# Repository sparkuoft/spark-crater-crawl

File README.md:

# spark-crater-crawl

Crater Crawl runs on **two Arduino Mega 2560s** joined by a serial cable. How it all
fits together, the wiring, and a step-by-step test plan are in
[docs/INTEGRATION.md](docs/INTEGRATION.md).

| Folder | What it is | Board |
| --- | --- | --- |
| `crater_crawl/` | Game sketch: game FSM, pillars and sequencer, LED strip, Serial console, unit tests | Game Mega |
| `crater_crawl_wheels/` | Wheels sketch (Alice): steering wheels, character steppers, plus Tracking's sensors | Wheels Mega |
| `hardware_tests/` | Small check sketches: LED strip, link cable, Tracking's inputs | either |
| `laptop/` | Runs the game sketch's logic on a computer, for testing without hardware | laptop |
| `Photo Interrupt Sensor/` | Tracking's PCB, tests and docs | |
| `demo/` | Demo script for the laptop build | |

## Arduino IDE setup

Board: **Arduino Mega or Mega 2560**. Install these from the Library Manager:
FastLED, TimerOne, TCA9548A, Servo.

Open `crater_crawl/crater_crawl.ino` and upload it to the Game Mega; open
`crater_crawl_wheels/crater_crawl_wheels.ino` and upload it to the Wheels Mega.
Serial Monitor: 115200 baud, "Newline". On the Game Mega, type `?` for status and
`t` to run the unit tests.

## Laptop build

    clang++ -std=c++11 -Wall -Wextra -pthread -Icrater_crawl/src -o test laptop/main.cpp crater_crawl/src/*.cpp
    ./test --test                              # unit tests
    ./test < demo/fall_design_review.txt       # demo round
    ./test --live                              # play in real time

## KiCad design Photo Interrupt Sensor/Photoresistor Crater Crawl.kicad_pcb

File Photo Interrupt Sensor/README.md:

# Character tracking (C)

> **Where the files are (2026-11-22):** `CharacterModule.h/.c` now live in
> `crater_crawl_wheels/src/tracking/`, because they're built into the Wheels Mega
> firmware. `CharacterController.*`, the tests and the PCB stay in this folder, and
> `tests/run_tests.py` finds the module in its new place. The hardware callbacks
> are in `crater_crawl_wheels/tracking_hal.cpp`. See `docs/INTEGRATION.md`.

`CharacterModule.c` and `CharacterController.c` implement the tracking logic in
C11 with fixed storage and no dynamic allocation. They do not include Arduino
or `shared_state.h`. C++ callers can include the headers directly because the
function declarations have `extern "C"` guards. Compile the `.c` files as C.

The physical pin mapping, encoder/mux driver, interrupt attachment and Wheels
transport are supplied through callbacks. No hardware driver or connection to
the existing game FSM/main loop is implemented here (those are the next step).

## Responsibilities

- One `CharacterModule` per player: encoder offset/angle validity, nonblocking
  homing, reference refresh and a queue of pillar-switch contact events.
- One `CharacterController` for the two players: updates both modules, validates
  the angle pair, detects circular proximity, and optionally requests a paired
  movement response. It never changes lives, lockouts or the game phase.
- The future game adapter publishes valid angles and drains both players'
  pillar queues before calling `game_fsm_update()`. Player-pair notifications
  are separate from pillar hits and must not be sent to `game_on_collision()`.

## Public API and initialization

Start with zero-initialized module/controller storage. Obtain a config with
`character_default_config()`, set player ID, actual encoder channel and hardware
callbacks, and check `character_init()`'s bool result. Initialization validates
configuration but does not access hardware or start motors. A failed init does
not modify the destination. Do not reinitialize active modules/controllers.

Provide all `CharacterHardware` callbacks except `identify_pillar`, which is
optional. A context pointer can hold the platform's player-to-pin and mux maps.
The input callbacks return logical **active/pressed**, so wiring polarity and
pull-up choices belong in the hardware adapter. Callbacks must be bounded and
nonblocking enough to meet the application's loop timing requirements.

Call `character_start_homing(player, now_ms)` explicitly. The start callback
must start controlled homing and report whether it succeeded; the stop callback
must stop it. Homing stops on success, timeout, reference-input failure or
`character_cancel_homing()`. Starting with the reference blocked requires a
clear observation followed by a new activation edge. It does not zero at an
arbitrary point inside the blocked region. A timeout/failure needs an explicit
retry; no automatic motor restart occurs. An encoder failure cannot produce a
valid angle and an unsuccessful homing attempt eventually times out.

Use `character_controller_update(controller, now_ms, collisions_enabled)` once
per loop. It calls both modules' updates; do not update them a second time.
Pass false during homing or when game rules forbid pair responses. Pillar
detection and reference tracking continue independently of that flag.

`character_get_angle()` returns a cached angle, not a fresh hardware read. Check
`character_angle_is_valid()` before using it. `character_is_calibrated()` only
means an offset was established: a later read failure invalidates the angle
without discarding that offset. The last valid cache is retained for diagnostics.

## Angle and reference contract

All angles are tenths of a degree, normalized to 0..3599. The adapter converts
raw encoder counts/gearing into an absolute character-ring angle. Configure
`encoder_sign` as +1 or -1 so both players use the same physical positive
direction and the same physical zero:

```text
angle_x10 = wrap3600(encoder_sign * (raw_angle_x10 - reference_offset_x10))
```

Both encoder callbacks receive the same configured mux channel. Normal reads
return a timestamped sample acquired at or before `now_ms`, within
`max_sample_age_ms`. Typically the adapter provides a recent cached acquisition
and the application timestamps its update after acquisition. Invalid/out-of-
range, stale or future samples do not update the cache or enable collisions.

Bind each hardware reference ACTIVATION interrupt to
`character_reference_isr(&player, crossing_ms)`. This only writes a first-edge
mailbox. Repeated edges while pending cannot replace the timestamp. The main
loop atomically takes the mailbox using the supplied critical-section callbacks;
on Mega these must save/disable/restore interrupt state. **No-op critical
callbacks are valid only in the single-threaded host tests.** Attach interrupts
after successful initialization and detach them before reinitializing/freeing
the module. The same module's ISR must not reenter itself.

`read_reference_sample` must return an actual acquisition near the crossing,
or a sample reconstructed at that time from sufficiently close samples. It must
not stamp a delayed reading with the old crossing timestamp. The module checks
the event age, sample timestamp and crossing/sample tolerance, rejects missing
or late data, and increments `rejected_reference_events`. It cannot verify the
truthfulness of a hardware adapter's timestamp. The adapter must document and
measure its acquisition/reconstruction error; the tests do not establish real
hardware timing. No I2C/mux operations run inside the ISR or critical section.

After calibration the reference is disarmed. It rearms only when the sensor is
clear and circular distance from zero is **strictly greater** than the buffer.
359 degrees is 1 degree from zero. Activation direction/flag width compensation
is deliberately deferred. Each accepted reference increments
`calibration_revision`, so the controller can distinguish an offset jump from
physical approach.

All timestamps use the same unsigned 32-bit millisecond clock. Duration checks
handle rollover; configured intervals are limited to `INT32_MAX`. Service the
loop regularly; timing bounds are not guarantees if callbacks or the caller
block. For sub-millisecond accuracy a finer hardware sampling strategy may be
necessary before integration.

## Pillar contacts

The first observed press is accepted immediately when armed, even if the angle
is unavailable. The switch remains latched while held and through release
bounce; only a stable released interval rearms it. This strategy does not filter
isolated noise pulses. By default an initially pressed switch is ignored until
stable release; `accept_initial_press` can change that policy.

Switches are polled. `hit_ms` is the first observation time, not an ISR edge
timestamp. The maximum loop interval must be shorter than the shortest physical
contact. If that cannot be demonstrated, add hardware edge capture in the
adapter before deployment; this implementation does not claim to capture
contacts entirely between polls. Failed switch reads require stable release
before accepting another press.

`character_read_pillar_collision()` consumes the oldest of four pending events.
Overflow preserves the oldest events and increments `dropped_pillar_events`.
Drain the queue each loop. Switches/queues are independent, so simultaneous hits
remain available for both players.

Attribution uses an optional direct `identify_pillar` callback first. Otherwise,
it uses a valid angle and a measured `pillar_angles_x10` table. Exactly one
pillar must match the tolerance; no match, overlapping matches or unavailable
angles produce `CHARACTER_UNKNOWN_PILLAR` (-1). This never suppresses the hit.
Do not cast -1 blindly into the game's uint8_t pillar ID: the future GL adapter
must agree an unknown-ID contract. Pillar phase/top-limit readings do not gate
contact detection.

## Player-pair collisions

The controller compares both fresh, valid angles only when their acquisition
timestamps are within `max_pair_sample_skew_ms`. It reports once at separation
**<= enter_x10**, and rearms at **> release_x10**. Initial overlap is suppressed
by default until players separate. That baseline policy also applies after
disabled detection or invalid/skewed data; `detect_initial_overlap=true` opts
into reporting overlap on those resumptions too.

When recalibration changes an established angle pair, no collision is reported
on that update. If the corrected pair is inside the release zone, separation is
required before another collision. This deliberately avoids interpreting an
offset correction as contact; it can suppress a real encounter coincident with
recalibration and should be evaluated in physical testing.

The pair event contains both positions and incoming directions captured before
any movement request. `character_controller_read_collision()` consumes the
pending pair notification. Each module also exposes a consuming
`character_read_character_collision()` notification. These are observations of
one encounter: **do not issue motor commands again from the per-player reads**.
Undrained notifications preserve the oldest event and expose overflow counters.

Default behavior is detection only. To opt into the proposed separation policy,
set `choose_response = character_response_separate`, supply `read_direction`
and `apply_response`, or supply your own policy. The built-in policy assigns
outgoing directions away from relative positions, handles head-on motion,
requires observed approach for same-direction catch-up, and declines already-
separating motion. At exact coincidence it uses previous ordering; if none is
available it declines. Unavailable directions also prevent a motor request.
An accepted policy calls `apply_response` once with both players. The adapter
must honor game eligibility, motor limits and command failures. The physical
response policy remains a team/playtesting decision.

## Provisional defaults

| Setting | Default |
| --- | --- |
| Reference rearm buffer | 45 degrees on either side of zero |
| Stable switch release | 20 ms |
| Homing timeout | 10 seconds |
| Maximum encoder sample age | 20 ms |
| Reference sample/crossing tolerance | 2 ms |
| Maximum queued reference event age | 20 ms |
| Pair entry / release thresholds | 5 / 10 degrees |
| Maximum pair sample skew | 5 ms |
| Initial switch press / initial pair overlap | Suppressed |
| Automatic pair movement response | Disabled |

These are starting values, not measurements. Tune acquisition latency against
maximum angular speed, and loop/debounce timing against measured contact width.

## Host verification from the VS Code PowerShell terminal

From the repository root with Python, GCC and G++ on PATH:

```powershell
python '.\Photo Interrupt Sensor\tests\run_tests.py'
```

The script compiles both production sources as C11 with warnings as errors,
runs 14 behavioral test groups, and links a C++ smoke test to the separately
compiled C objects. Outputs go into ignored `build/tracking-tests/`. It does
not build the incomplete game application or upload firmware. Compiler paths
can be passed with `--cc` and `--cxx`. The Python runner also works from Windows
PowerShell installations that restrict execution of `.ps1` scripts, without
changing the shell's execution policy.

The VS Code `windows-gcc-x64` IntelliSense configuration uses this computer's
MSYS2 GCC; the existing macOS configuration is preserved. Select the Windows
configuration locally if VS Code still reports `/usr/bin/clang` errors. Editor
IntelliSense selection does not change how the test script compiles the files.

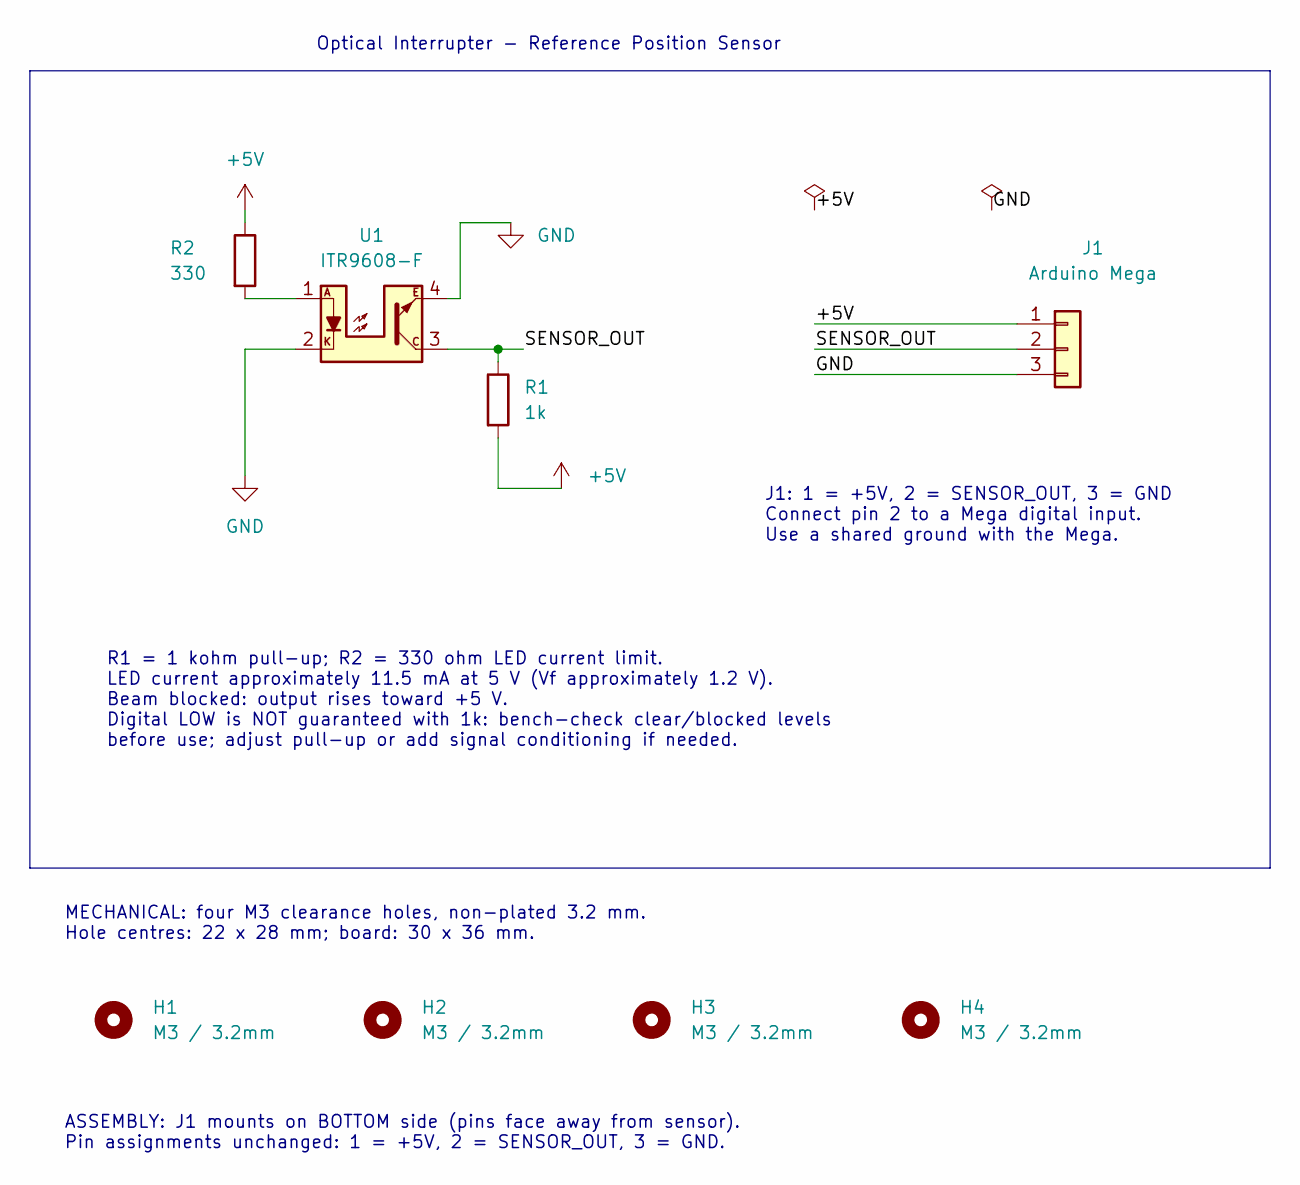
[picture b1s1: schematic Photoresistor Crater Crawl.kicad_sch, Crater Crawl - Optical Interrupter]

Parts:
H1, H2, H3, H4: M3 / 3.2mm; MountingHole_3.2mm_M3
J1: Arduino Mega; PinHeader_1x03_P2.54mm_Vertical
R1: 1k; R_Axial_DIN0207_L6.3mm_D2.5mm_P7.62mm_Horizontal
R2: 330; R_Axial_DIN0207_L6.3mm_D2.5mm_P7.62mm_Horizontal
U1: ITR9608-F; Everlight_ITR9608-F_EdgeSlot

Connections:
+5V: J1.1, R1.2, R2.1
/SENSOR_OUT: J1.2, R1.1, U1.3
GND: J1.3, U1.2, U1.4
unnamed: R2.2, U1.1

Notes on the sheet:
ASSEMBLY: J1 mounts on BOTTOM side (pins face away from sensor). Pin assignments unchanged: 1 = +5V, 2 = SENSOR_OUT, 3 = GND.
Optical Interrupter - Reference Position Sensor
J1: 1 = +5V, 2 = SENSOR_OUT, 3 = GND Connect pin 2 to a Mega digital input. Use a shared ground with the Mega.
R1 = 1 kohm pull-up; R2 = 330 ohm LED current limit. LED current approximately 11.5 mA at 5 V (Vf approximately 1.2 V). Beam blocked: output rises toward +5 V. Digital LOW is NOT guaranteed with 1k: bench-check clear/blocked levels before use; adjust pull-up or add signal conditioning if needed.
MECHANICAL: four M3 clearance holes, non-plated 3.2 mm. Hole centres: 22 x 28 mm; board: 30 x 36 mm.

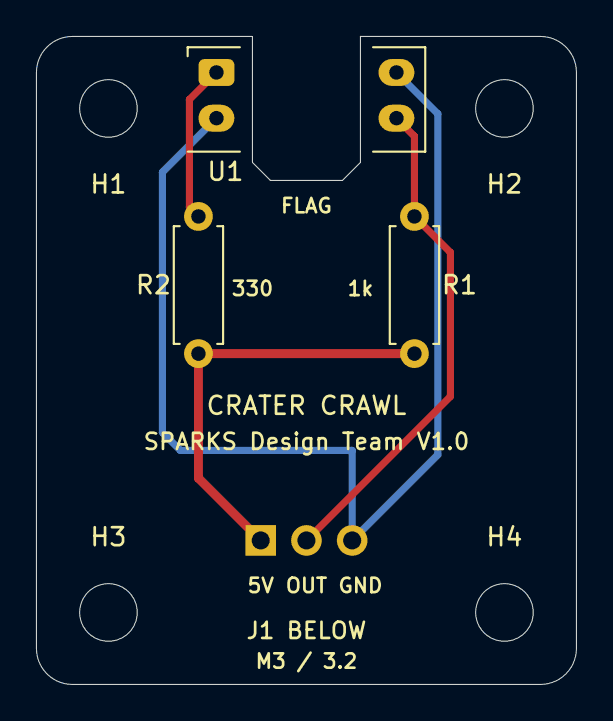
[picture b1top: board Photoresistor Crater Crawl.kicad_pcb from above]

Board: 2 copper layers, 30.0 x 36.0 mm, 8 parts (1 on the bottom side), 4 nets.
